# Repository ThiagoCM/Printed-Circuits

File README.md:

# Printed-Circuits
Projects and files related to the 2016.2 class at Universidade Federal de Alagoas

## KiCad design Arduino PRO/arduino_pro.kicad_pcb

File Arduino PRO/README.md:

On this project we should use Kicad to create a schematic and PCB for an Arduino PRO.
Project Rules:

- Os pinos de alimentação devem chegar na placa através de conectores com parafuso [0,10]
- A placa deve ter ser 25x25mm [0,40]
- A expessura das trilhas de alimentação devem seguir as regras de cálculo definidos pelo site: http://circuitcalculator.com/wordpress/2006/01/31/pcb-trace-width-calculator/ supondo que usaremos os materiais padrão da PCBWay. [0,30]

- 6 mil minimum trace width
- 6 mil minimum spacing
- at least 15 mil clearances from traces to the edge of the board
- 13 mil minimum drill size
- 7 mil minimum annular ring

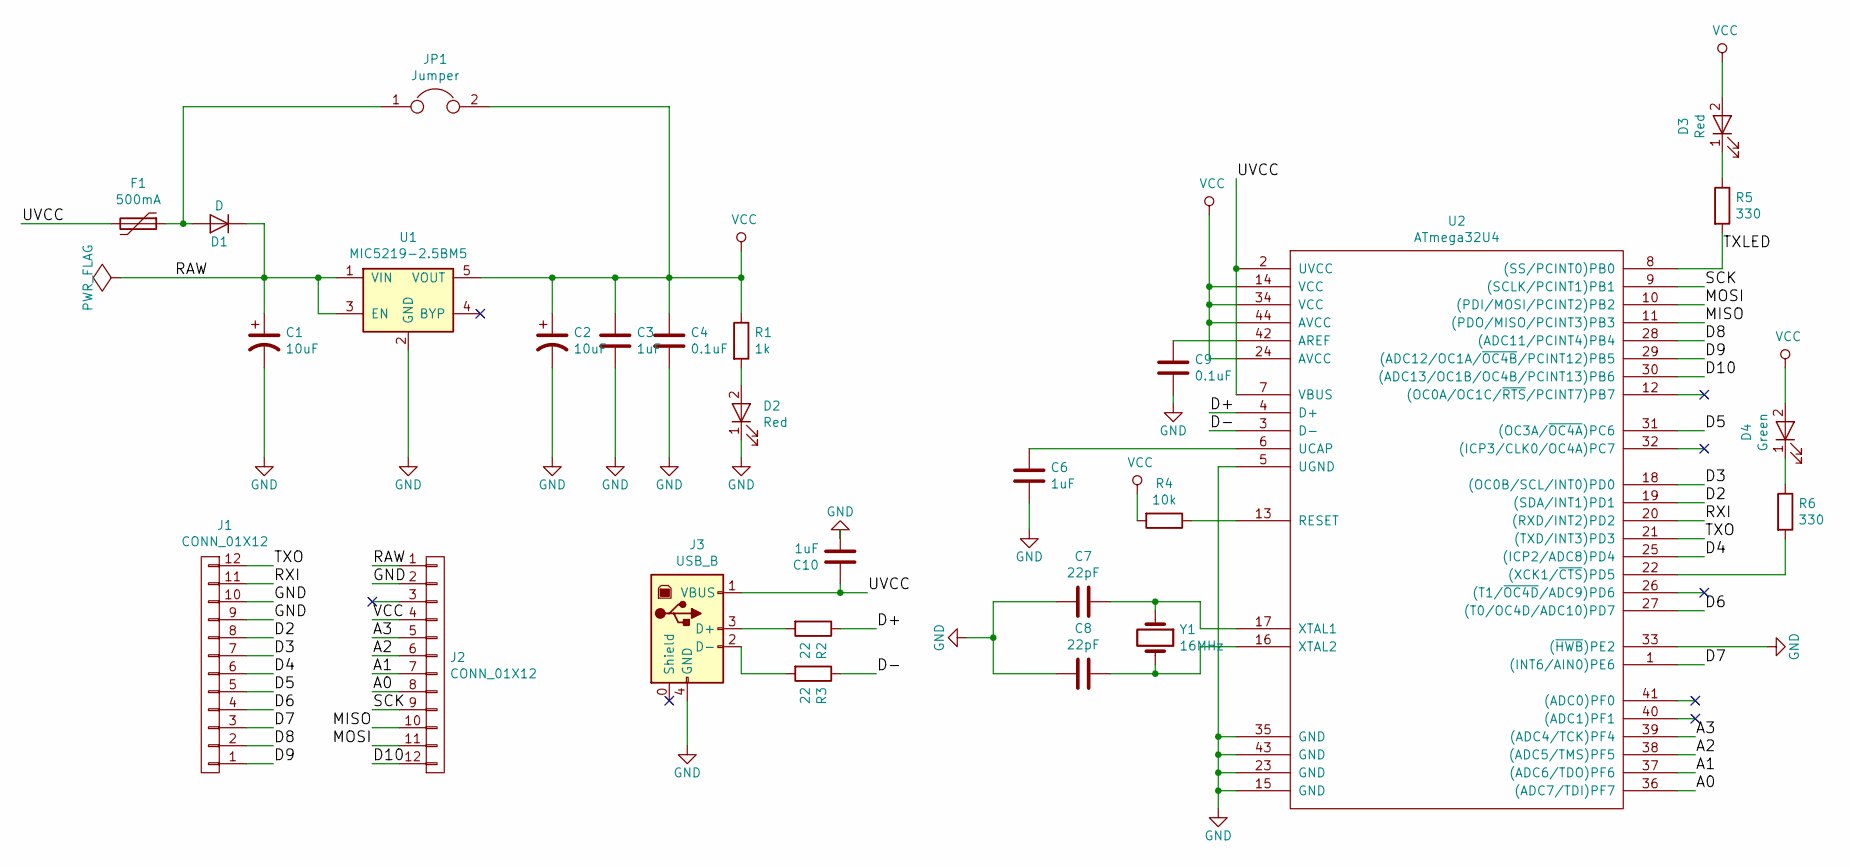
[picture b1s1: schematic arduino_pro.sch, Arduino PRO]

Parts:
C1, C2: 10uF; CP_Tantalum_Case-B_EIA-3528-21_Hand
C3, C6, C10: 1uF; C_0402
C4, C9: 0.1uF; C_0402
C7, C8: 22pF; C_0402
D1: D; D_0603
D2, D3: Red; LED_0402
D4: Green; LED_0402
F1: 500mA; Fuse_SMD1206_HandSoldering
J1, J2: CONN_01X12; Socket_Strip_Straight_1x12_Pitch1.27mm
J3: USB_B; USB_Micro-B
JP1: Jumper; GS2
R1: 1k; R_0402
R2, R3: 22; R_0402
R4: 10k; R_0402
R5, R6: 330; R_0402
U1: MIC5219-2.5BM5; SOT-23-5
U2: ATmega32U4; MLF-44_Atmel
Y1: 16MHz; Crystal_SMD_3225-4pin_3.2x2.5mm_HandSoldering

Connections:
/A0: J2.8, U2.36 ((ADC7/TDI)PF7)
/A1: J2.7, U2.37 ((ADC6/TDO)PF6)
/A2: J2.6, U2.38 ((ADC5/TMS)PF5)
/A3: J2.5, U2.39 ((ADC4/TCK)PF4)
/D2: J1.8, U2.19 ((SDA/INT1)PD1)
/D3: J1.7, U2.18 ((OC0B/SCL/INT0)PD0)
/D4: J1.6, U2.25 ((ICP2/ADC8)PD4)
/D5: J1.5, U2.31 ((OC3A/~OC4A~)PC6)
/D6: J1.4, U2.27 ((T0/OC4D/ADC10)PD7)
/D7: J1.3, U2.1 ((INT6/AIN0)PE6)
/D8: J1.2, U2.28 ((ADC11/PCINT4)PB4)
/D9: J1.1, U2.29 ((ADC12/OC1A/~OC4B~/PCINT12)PB5)
/D10: J2.12, U2.30 ((ADC13/OC1B/OC4B/PCINT13)PB6)
/D+: R2.1, U2.4 (D+)
/D-: R3.1, U2.3 (D-)
/MISO: J2.10, U2.11 ((PDO/MISO/PCINT3)PB3)
/MOSI: J2.11, U2.10 ((PDI/MOSI/PCINT2)PB2)
/RAW: C1.1, D1.1 (K), J2.1, U1.1 (VIN), U1.3 (EN)
/RXI: J1.11, U2.20 ((RXD/INT2)PD2)
/SCK: J2.9, U2.9 ((SCLK/PCINT1)PB1)
/TXLED: R5.2, U2.8 ((SS/PCINT0)PB0)
/TXO: J1.12, U2.21 ((TXD/INT3)PD3)
/UVCC: C10.1, F1.2, J3.1 (VBUS), U2.2 (UVCC), U2.7 (VBUS)
GND: C1.2, C2.2, C3.2, C4.2, C6.2, C7.2, C8.2, C9.2, C10.2, D2.1 (K), J1.9, J1.10, J2.2, J3.4 (GND), U1.2 (GND), U2.5 (UGND), U2.15 (GND), U2.23 (GND), U2.33 ((~HWB~)PE2), U2.35 (GND), U2.43 (GND)
unnamed: C6.1, U2.6 (UCAP)
unnamed: C7.1, U2.17 (XTAL1), Y1.1
unnamed: C8.1, U2.16 (XTAL2), Y1.2
unnamed: C9.1, U2.42 (AREF)
unnamed: D1.2 (A), F1.1, JP1.1
unnamed: D2.2 (A), R1.2
unnamed: D3.1 (K), R5.1
unnamed: D4.1 (K), R6.1
unnamed: J3.2 (D-), R3.2
unnamed: J3.3 (D+), R2.2
unnamed: R4.1, U2.13 (RESET)
unnamed: R6.2, U2.22 ((XCK1/~CTS~)PD5)
VCC: C2.1, C3.1, C4.1, D3.2 (A), D4.2 (A), J2.4, JP1.2, R1.1, R4.2, U1.5 (VOUT), U2.14 (VCC), U2.24 (AVCC), U2.34 (VCC), U2.44 (AVCC)

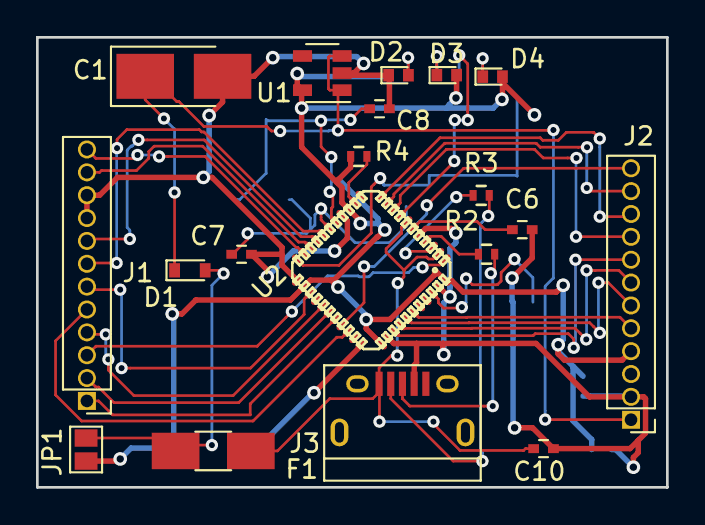
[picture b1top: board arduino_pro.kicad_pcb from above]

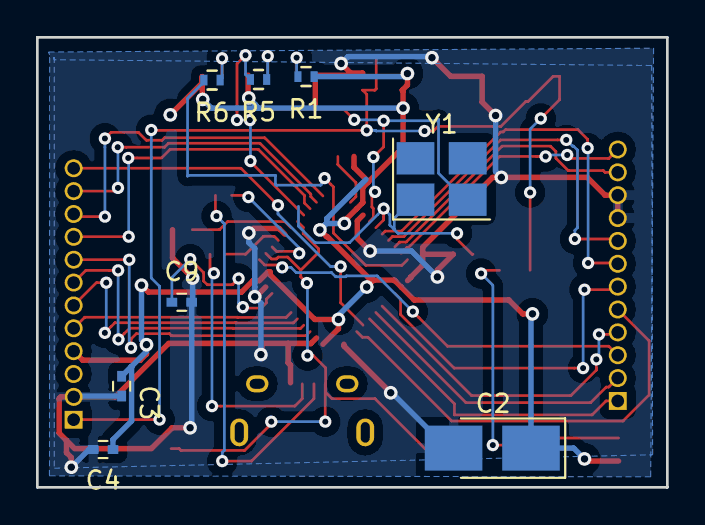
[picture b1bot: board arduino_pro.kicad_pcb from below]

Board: 2 copper layers, 35.0 x 25.0 mm, 27 parts (8 on the bottom side), 37 nets.

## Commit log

2017-03-01 Creating an image archive
